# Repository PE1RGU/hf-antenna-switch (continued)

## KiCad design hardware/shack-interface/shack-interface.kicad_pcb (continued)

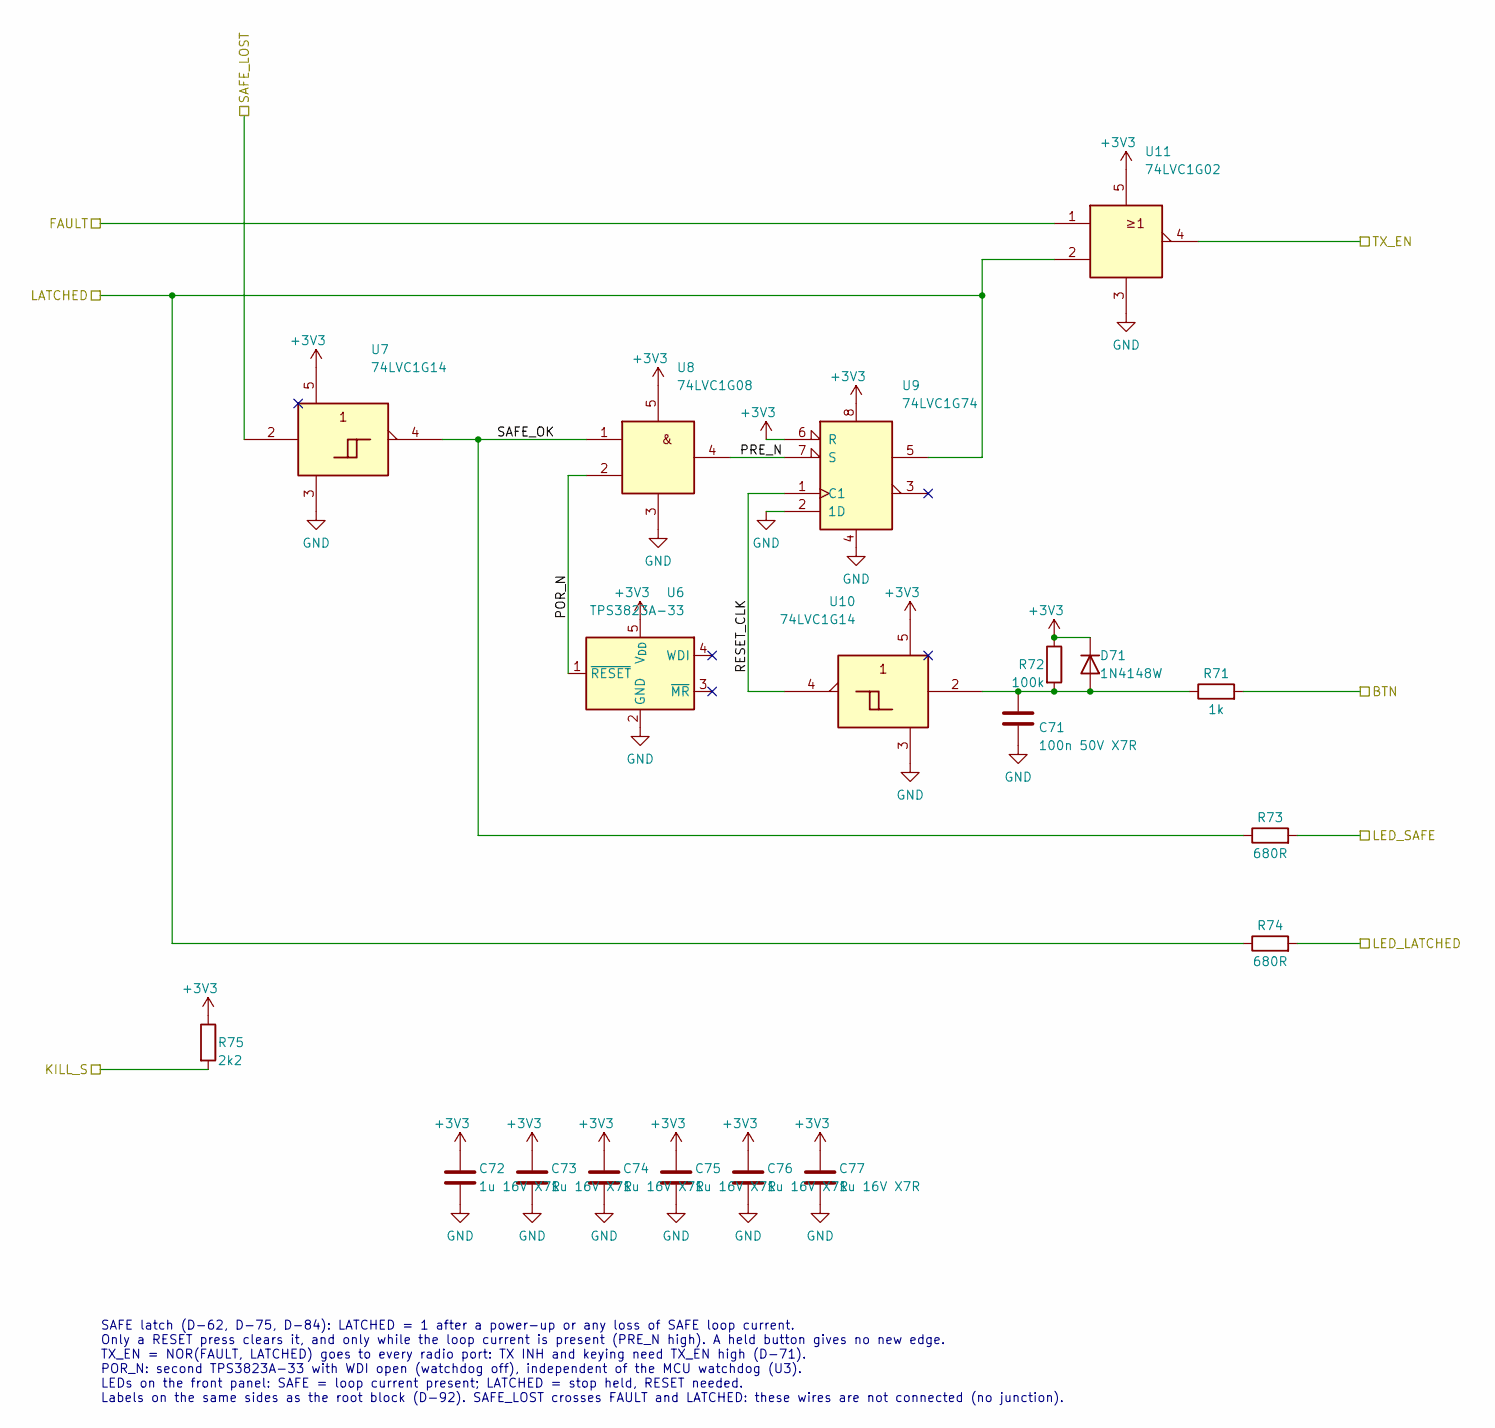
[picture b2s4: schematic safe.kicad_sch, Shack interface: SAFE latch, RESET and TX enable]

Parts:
C71: 100n 50V X7R; C_0603_1608Metric_Pad1.08x0.95mm_HandSolder
C72, C73, C74, C75, C76, C77: 1u 16V X7R; C_0603_1608Metric_Pad1.08x0.95mm_HandSolder
D71: 1N4148W; D_SOD-123; MPN 1N4148W
R71: 1k; R_0603_1608Metric_Pad0.98x0.95mm_HandSolder
R72: 100k; R_0603_1608Metric_Pad0.98x0.95mm_HandSolder
R73, R74: 680R; R_0603_1608Metric_Pad0.98x0.95mm_HandSolder
R75: 2k2; R_0603_1608Metric_Pad0.98x0.95mm_HandSolder
U6: TPS3823A-33; SOT-23-5; MPN TPS3823A-33DBVR
U7, U10: 74LVC1G14; SOT-23-5; MPN 74LVC1G14GV
U8: 74LVC1G08; SOT-23-5; MPN 74LVC1G08GV
U9: 74LVC1G74; VSSOP-8_2.3x2mm_P0.5mm; MPN SN74LVC1G74DCUR
U11: 74LVC1G02; SOT-23-5; MPN 74LVC1G02GV

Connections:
+3V3: C72.1, C73.1, C74.1, C75.1, C76.1, C77.1, D71.1 (K), R72.1, R75.1, U6.5 (V_{DD}), U7.5, U8.5, U9.6 (R), U9.8, U10.5, U11.5; also elsewhere on the board
/MCU and expander/FAULT: U11.1; also elsewhere on the board
/MCU and expander/KILL_S: R75.2; also elsewhere on the board
/MCU and expander/LATCHED: R74.1, U9.5, U11.2; also elsewhere on the board
/MCU and expander/SAFE_LOST: U7.2; also elsewhere on the board
/Radio port R1/TX_EN: U11.4; also elsewhere on the board
/SAFE latch/BTN: R71.2; also elsewhere on the board
/SAFE latch/LED_LATCHED: R74.2; also elsewhere on the board
/SAFE latch/LED_SAFE: R73.2; also elsewhere on the board
/SAFE latch/POR_N: U6.1 (~RESET), U8.2
/SAFE latch/PRE_N: U8.4, U9.7 (S)
/SAFE latch/RESET_CLK: U9.1 (C1), U10.4
/SAFE latch/SAFE_OK: R73.1, U7.4, U8.1
GND: C71.2, C72.2, C73.2, C74.2, C75.2, C76.2, C77.2, U6.2 (GND), U7.3, U8.3, U9.2 (1D), U9.4, U10.3, U11.3; also elsewhere on the board
unnamed: C71.1, D71.2 (A), R71.1, R72.2, U10.2

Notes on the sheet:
SAFE latch (D-62, D-75, D-84): LATCHED = 1 after a power-up or any loss of SAFE loop current. Only a RESET press clears it, and only while the loop current is present (PRE_N high). A held button gives no new edge. TX_EN = NOR(FAULT, LATCHED) goes to every radio port: TX INH and keying need TX_EN hi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

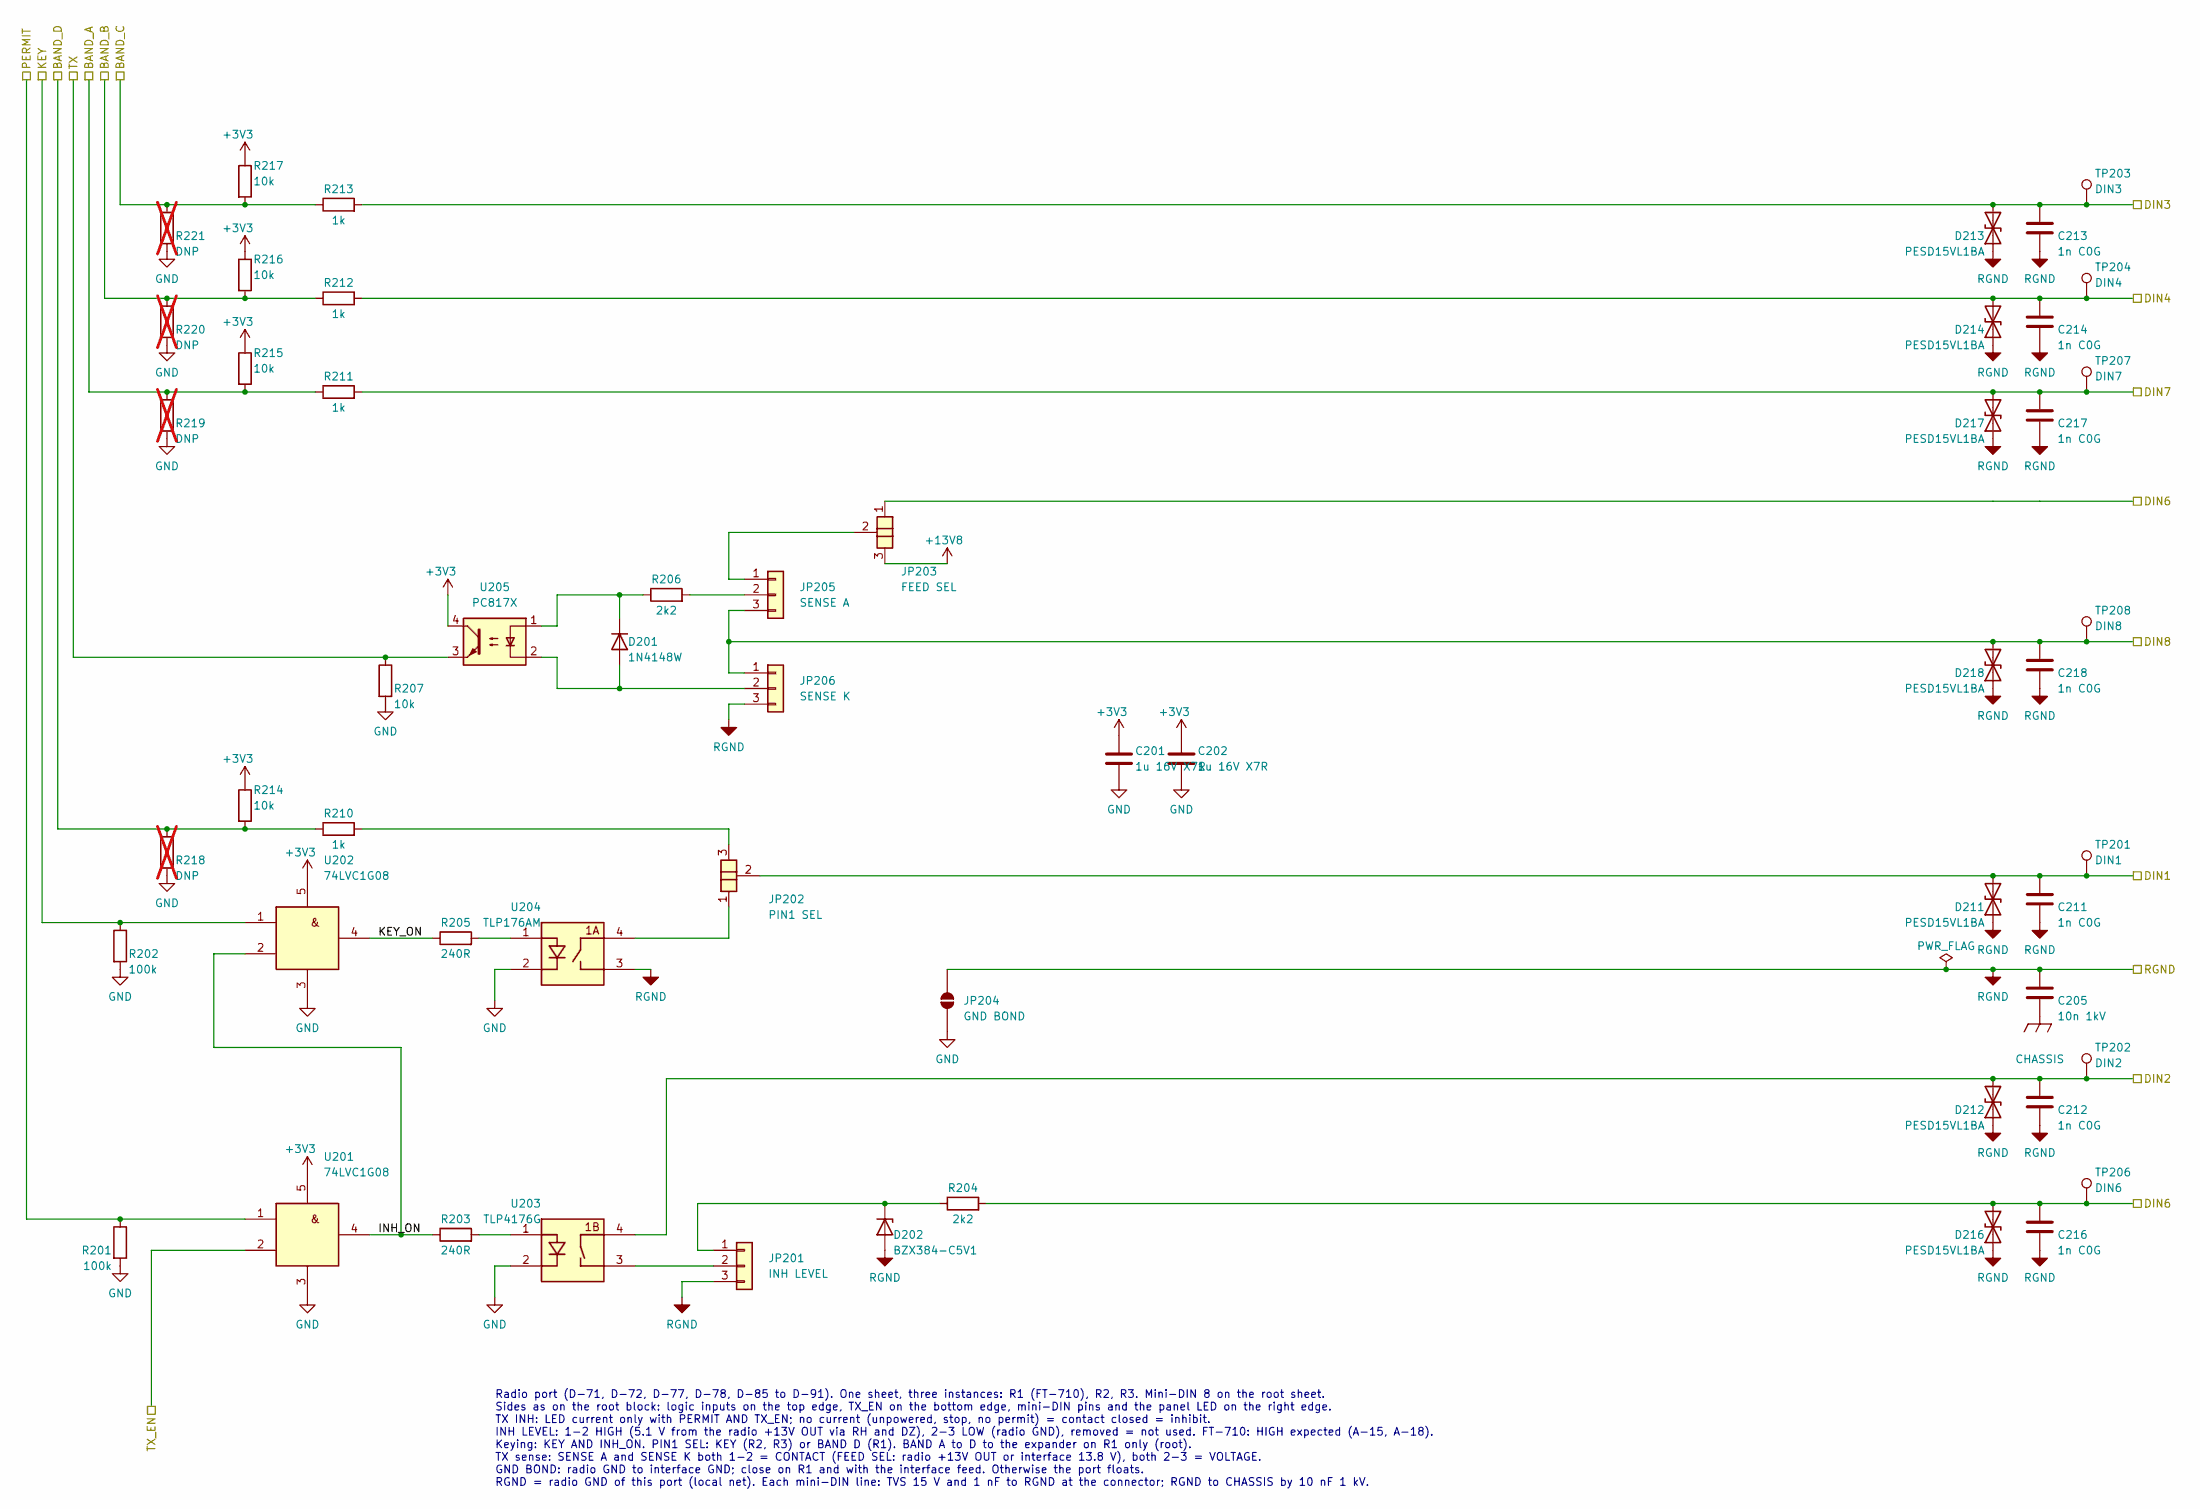
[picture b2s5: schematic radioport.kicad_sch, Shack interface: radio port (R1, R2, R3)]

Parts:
C201, C202: 1u 16V X7R; C_0603_1608Metric_Pad1.08x0.95mm_HandSolder
C205: 10n 1kV; C_1206_3216Metric_Pad1.33x1.80mm_HandSolder
C211, C212, C213, C214, C216, C217, C218: 1n C0G; C_0603_1608Metric_Pad1.08x0.95mm_HandSolder
D201: 1N4148W; D_SOD-123; MPN 1N4148W
D202: BZX384-C5V1; D_SOD-323_HandSoldering; MPN BZX384-C5V1
D211, D212, D213, D214, D216, D217, D218: PESD15VL1BA; D_SOD-323_HandSoldering; MPN PESD15VL1BA
JP201: INH LEVEL; PinHeader_1x03_P2.54mm_Vertical
JP202: PIN1 SEL; SolderJumper-3_P1.3mm_Open_RoundedPad1.0x1.5mm_NumberLabels
JP203: FEED SEL; SolderJumper-3_P1.3mm_Open_RoundedPad1.0x1.5mm_NumberLabels
JP204: GND BOND; SolderJumper-2_P1.3mm_Open_RoundedPad1.0x1.5mm
JP205: SENSE A; PinHeader_1x03_P2.54mm_Vertical
JP206: SENSE K; PinHeader_1x03_P2.54mm_Vertical
R201, R202: 100k; R_0603_1608Metric_Pad0.98x0.95mm_HandSolder
R203, R205: 240R; R_0603_1608Metric_Pad0.98x0.95mm_HandSolder
R204: 2k2; R_0603_1608Metric_Pad0.98x0.95mm_HandSolder
R206: 2k2; R_1206_3216Metric_Pad1.30x1.75mm_HandSolder
R207, R214, R215, R216, R217: 10k; R_0603_1608Metric_Pad0.98x0.95mm_HandSolder
R210, R211, R212, R213: 1k; R_0603_1608Metric_Pad0.98x0.95mm_HandSolder
R218, R219, R220, R221: DNP; R_0603_1608Metric_Pad0.98x0.95mm_HandSolder; not fitted
TP201: DIN1; TestPoint_Pad_D1.5mm
TP202: DIN2; TestPoint_Pad_D1.5mm
TP203: DIN3; TestPoint_Pad_D1.5mm
TP204: DIN4; TestPoint_Pad_D1.5mm
TP206: DIN6; TestPoint_Pad_D1.5mm
TP207: DIN7; TestPoint_Pad_D1.5mm
TP208: DIN8; TestPoint_Pad_D1.5mm
U201, U202: 74LVC1G08; SOT-23-5; MPN 74LVC1G08GV
U203: TLP4176G; SOP-4_P2.54mm_PhotoRelay_LongPad; MPN TLP4176G
U204: TLP176AM; SOP-4_P2.54mm_PhotoRelay_LongPad; MPN TLP176AM(TPL,E)
U205: PC817X; DIP-4_W7.62mm; MPN PC817X2NSZ9F

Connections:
+3V3: C201.1, C202.1, R214.1, R215.1, R216.1, R217.1, U201.5, U202.5, U205.4; also elsewhere on the board
+13V8: JP203.3; also elsewhere on the board
/Link to the box/R1_TX: R207.1, U205.3; also elsewhere on the board
/MCU and expander/BAND_A: R211.1, R215.2, R219.1; also elsewhere on the board
/MCU and expander/BAND_B: R212.1, R216.2, R220.1; also elsewhere on the board
/MCU and expander/BAND_C: R213.1, R217.2, R221.1; also elsewhere on the board
/MCU and expander/BAND_D: R210.1, R214.2, R218.1; also elsewhere on the board
/MCU and expander/KEY_R1: R202.1, U202.1; also elsewhere on the board
/MCU and expander/PERMIT_R1: R201.1, U201.1; also elsewhere on the board
/Radio port R1/DIN1: C211.1, D211.2 (A2), JP202.2, TP201.1; also elsewhere on the board
/Radio port R1/DIN2: C212.1, D212.2 (A2), TP202.1, U203.4; also elsewhere on the board
/Radio port R1/DIN3: C213.1, D213.2 (A2), R213.2, TP203.1; also elsewhere on the board
/Radio port R1/DIN4: C214.1, D214.2 (A2), R212.2, TP204.1; also elsewhere on the board
/Radio port R1/DIN6: C216.1, D216.2 (A2), JP203.1, R204.2, TP206.1; also elsewhere on the board
/Radio port R1/DIN7: C217.1, D217.2 (A2), R211.2, TP207.1; also elsewhere on the board
/Radio port R1/DIN8: C218.1, D218.2 (A2), JP205.3, JP206.1, TP208.1; also elsewhere on the board
/Radio port R1/INH_ON: R203.1, U201.4, U202.2
/Radio port R1/KEY_ON: R205.1, U202.4
/Radio port R1/RGND: C205.1, C211.2, C212.2, C213.2, C214.2, C216.2, C217.2, C218.2, D202.2 (A), D211.1 (A1), D212.1 (A1), D213.1 (A1), D214.1 (A1), D216.1 (A1), D217.1 (A1), D218.1 (A1), JP201.3, JP204.2 (B), JP206.3, U204.3; also elsewhere on the board
/Radio port R1/TX_EN: U201.2; also elsewhere on the board
CHASSIS: C205.2; also elsewhere on the board
GND: C201.2, C202.2, JP204.1 (A), R201.2, R202.2, R207.2, R218.2, R219.2, R220.2, R221.2, U201.3, U202.3, U203.2, U204.2; also elsewhere on the board
unnamed: D201.2 (A), JP206.2, U205.2
unnamed: D201.1 (K), R206.1, U205.1
unnamed: D202.1 (K), JP201.1, R204.1
unnamed: JP201.2, U203.3
unnamed: JP202.1, U204.4
unnamed: JP202.3, R210.2
unnamed: JP203.2, JP205.1
unnamed: JP205.2, R206.2
unnamed: R203.2, U203.1
unnamed: R205.2, U204.1

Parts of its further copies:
C301, C302, C401, C402: 1u 16V X7R; C_0603_1608Metric_Pad1.08x0.95mm_HandSolder
C305, C405: 10n 1kV; C_1206_3216Metric_Pad1.33x1.80mm_HandSolder
C311, C312, C313, C314, C316, C317, C318, C411, C412, C413, C414, C416, C417, C418: 1n C0G; C_0603_1608Metric_Pad1.08x0.95mm_HandSolder
D301, D401: 1N4148W; D_SOD-123; MPN 1N4148W
D302, D402: BZX384-C5V1; D_SOD-323_HandSoldering; MPN BZX384-C5V1
D311, D312, D313, D314, D316, D317, D318, D411, D412, D413, D414, D416, D417, D418: PESD15VL1BA; D_SOD-323_HandSoldering; MPN PESD15VL1BA
JP301, JP401: INH LEVEL; PinHeader_1x03_P2.54mm_Vertical
JP302, JP402: PIN1 SEL; SolderJumper-3_P1.3mm_Open_RoundedPad1.0x1.5mm_NumberLabels
JP303, JP403: FEED SEL; SolderJumper-3_P1.3mm_Open_RoundedPad1.0x1.5mm_NumberLabels
JP304, JP404: GND BOND; SolderJumper-2_P1.3mm_Open_RoundedPad1.0x1.5mm
JP305, JP405: SENSE A; PinHeader_1x03_P2.54mm_Vertical
JP306, JP406: SENSE K; PinHeader_1x03_P2.54mm_Vertical
R301, R302, R401, R402: 100k; R_0603_1608Metric_Pad0.98x0.95mm_HandSolder
R303, R305, R403, R405: 240R; R_0603_1608Metric_Pad0.98x0.95mm_HandSolder
R304, R404: 2k2; R_0603_1608Metric_Pad0.98x0.95mm_HandSolder
R306, R406: 2k2; R_1206_3216Metric_Pad1.30x1.75mm_HandSolder
R307, R314, R315, R316, R317, R407, R414, R415, R416, R417: 10k; R_0603_1608Metric_Pad0.98x0.95mm_HandSolder
R310, R311, R312, R313, R410, R411, R412, R413: 1k; R_0603_1608Metric_Pad0.98x0.95mm_HandSolder
R318, R319, R320, R321, R418, R419, R420, R421: DNP; R_0603_1608Metric_Pad0.98x0.95mm_HandSolder; not fitted
TP301, TP401: DIN1; TestPoint_Pad_D1.5mm
TP302, TP402: DIN2; TestPoint_Pad_D1.5mm
TP303, TP403: DIN3; TestPoint_Pad_D1.5mm
TP304, TP404: DIN4; TestPoint_Pad_D1.5mm
TP306, TP406: DIN6; TestPoint_Pad_D1.5mm
TP307, TP407: DIN7; TestPoint_Pad_D1.5mm
TP308, TP408: DIN8; TestPoint_Pad_D1.5mm
U301, U302, U401, U402: 74LVC1G08; SOT-23-5; MPN 74LVC1G08GV
U303, U403: TLP4176G; SOP-4_P2.54mm_PhotoRelay_LongPad; MPN TLP4176G
U304, U404: TLP176AM; SOP-4_P2.54mm_PhotoRelay_LongPad; MPN TLP176AM(TPL,E)
U305, U405: PC817X; DIP-4_W7.62mm; MPN PC817X2NSZ9F

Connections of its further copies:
+3V3: C301.1, C302.1, C401.1, C402.1, R314.1, R315.1, R316.1, R317.1, R414.1, R415.1, R416.1, R417.1, U301.5, U302.5, U305.4, U401.5, U402.5, U405.4; also elsewhere on the board
+13V8: JP303.3, JP403.3; also elsewhere on the board
/MCU and expander/KEY_R2: R302.1, U302.1; also elsewhere on the board
/MCU and expander/KEY_R3: R402.1, U402.1; also elsewhere on the board
/MCU and expander/PERMIT_R2: R301.1, U301.1; also elsewhere on the board
/MCU and expander/PERMIT_R3: R401.1, U401.1; also elsewhere on the board
/MCU and expander/R2_TX: R307.1, U305.3; also elsewhere on the board
/MCU and expander/R3_TX: R407.1, U405.3; also elsewhere on the board
/Radio port R1/TX_EN: U301.2, U401.2; also elsewhere on the board
/Radio port R2/BAND_A: R311.1, R315.2, R319.1
/Radio port R2/BAND_B: R312.1, R316.2, R320.1
/Radio port R2/BAND_C: R313.1, R317.2, R321.1
/Radio port R2/BAND_D: R310.1, R314.2, R318.1
/Radio port R2/DIN1: C311.1, D311.2 (A2), JP302.2, TP301.1; also elsewhere on the board
/Radio port R2/DIN2: C312.1, D312.2 (A2), TP302.1, U303.4; also elsewhere on the board
/Radio port R2/DIN3: C313.1, D313.2 (A2), R313.2, TP303.1; also elsewhere on the board
/Radio port R2/DIN4: C314.1, D314.2 (A2), R312.2, TP304.1; also elsewhere on the board
/Radio port R2/DIN6: C316.1, D316.2 (A2), JP303.1, R304.2, TP306.1; also elsewhere on the board
/Radio port R2/DIN7: C317.1, D317.2 (A2), R311.2, TP307.1; also elsewhere on the board
/Radio port R2/DIN8: C318.1, D318.2 (A2), JP305.3, JP306.1, TP308.1; also elsewhere on the board
/Radio port R2/INH_ON: R303.1, U301.4, U302.2
/Radio port R2/KEY_ON: R305.1, U302.4
/Radio port R2/RGND: C305.1, C311.2, C312.2, C313.2, C314.2, C316.2, C317.2, C318.2, D302.2 (A), D311.1 (A1), D312.1 (A1), D313.1 (A1), D314.1 (A1), D316.1 (A1), D317.1 (A1), D318.1 (A1), JP301.3, JP304.2 (B), JP306.3, U304.3; also elsewhere on the board
/Radio port R3/BAND_A: R411.1, R415.2, R419.1
/Radio port R3/BAND_B: R412.1, R416.2, R420.1
/Radio port R3/BAND_C: R413.1, R417.2, R421.1
/Radio port R3/BAND_D: R410.1, R414.2, R418.1
/Radio port R3/DIN1: C411.1, D411.2 (A2), JP402.2, TP401.1; also elsewhere on the board
/Radio port R3/DIN2: C412.1, D412.2 (A2), TP402.1, U403.4; also elsewhere on the board
/Radio port R3/DIN3: C413.1, D413.2 (A2), R413.2, TP403.1; also elsewhere on the board
/Radio port R3/DIN4: C414.1, D414.2 (A2), R412.2, TP404.1; also elsewhere on the board
/Radio port R3/DIN6: C416.1, D416.2 (A2), JP403.1, R404.2, TP406.1; also elsewhere on the board
/Radio port R3/DIN7: C417.1, D417.2 (A2), R411.2, TP407.1; also elsewhere on the board
/Radio port R3/DIN8: C418.1, D418.2 (A2), JP405.3, JP406.1, TP408.1; also elsewhere on the board
/Radio port R3/INH_ON: R403.1, U401.4, U402.2
/Radio port R3/KEY_ON: R405.1, U402.4
/Radio port R3/RGND: C405.1, C411.2, C412.2, C413.2, C414.2, C416.2, C417.2, C418.2, D402.2 (A), D411.1 (A1), D412.1 (A1), D413.1 (A1), D414.1 (A1), D416.1 (A1), D417.1 (A1), D418.1 (A1), JP401.3, JP404.2 (B), JP406.3, U404.3; also elsewhere on the board
CHASSIS: C305.2, C405.2; also elsewhere on the board
GND: C301.2, C302.2, C401.2, C402.2, JP304.1 (A), JP404.1 (A), R301.2, R302.2, R307.2, R318.2, R319.2, R320.2, R321.2, R401.2, R402.2, R407.2, R418.2, R419.2, R420.2, R421.2, U301.3, U302.3, U303.2, U304.2, U401.3, U402.3, U403.2, U404.2; also elsewhere on the board
unnamed: D301.2 (A), JP306.2, U305.2
unnamed: D301.1 (K), R306.1, U305.1
unnamed: D302.1 (K), JP301.1, R304.1
unnamed: D401.2 (A), JP406.2, U405.2
unnamed: D401.1 (K), R406.1, U405.1
unnamed: D402.1 (K), JP401.1, R404.1
unnamed: JP301.2, U303.3
unnamed: JP302.1, U304.4
unnamed: JP302.3, R310.2
unnamed: JP303.2, JP305.1
unnamed: JP305.2, R306.2
unnamed: JP401.2, U403.3
unnamed: JP402.1, U404.4
unnamed: JP402.3, R410.2
unnamed: JP403.2, JP405.1
unnamed: JP405.2, R406.2
unnamed: R303.2, U303.1
unnamed: R305.2, U304.1
unnamed: R403.2, U403.1
unnamed: R405.2, U404.1

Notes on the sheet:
Radio port (D-71, D-72, D-77, D-78, D-85 to D-91). One sheet, three instances: R1 (FT-710), R2, R3. Mini-DIN 8 on the root sheet. Sides as on the root block: logic inputs on the top edge, TX_EN on the bottom edge, mini-DIN pins and the panel LED on the right edge. TX INH: LED current only with PERM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

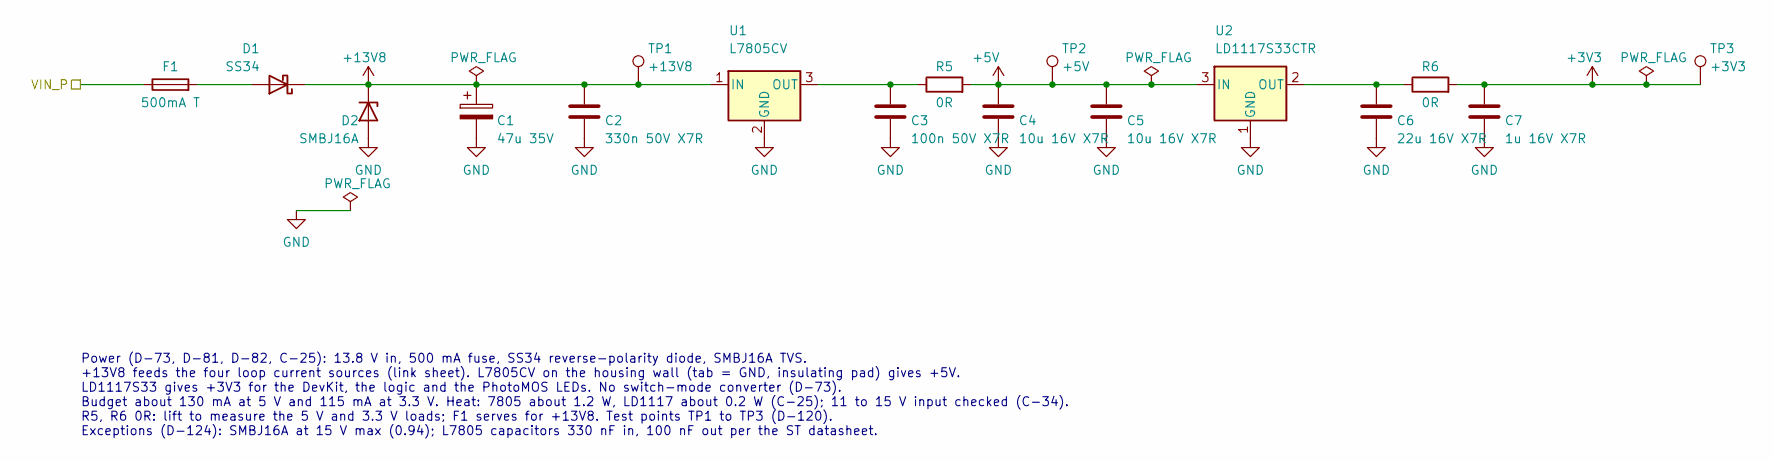
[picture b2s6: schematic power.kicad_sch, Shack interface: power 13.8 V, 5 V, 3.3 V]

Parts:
C1: 47u 35V; CP_Radial_D6.3mm_P2.50mm
C2: 330n 50V X7R; C_0805_2012Metric_Pad1.18x1.45mm_HandSolder
C3: 100n 50V X7R; C_0603_1608Metric_Pad1.08x0.95mm_HandSolder
C4, C5: 10u 16V X7R; C_1206_3216Metric_Pad1.33x1.80mm_HandSolder
C6: 22u 16V X7R; C_1210_3225Metric_Pad1.33x2.70mm_HandSolder
C7: 1u 16V X7R; C_0603_1608Metric_Pad1.08x0.95mm_HandSolder
D1: SS34; D_SMC; MPN SS34-M3/57T
D2: SMBJ16A; D_SMB; MPN SMBJ16A
F1: 500mA T; Fuse_1206_3216Metric; MPN SF-1206S050
R5, R6: 0R; R_1206_3216Metric_Pad1.30x1.75mm_HandSolder
TP1: +13V8; TestPoint_Pad_D1.5mm
TP2: +5V; TestPoint_Pad_D1.5mm
TP3: +3V3; TestPoint_Pad_D1.5mm
U1: L7805CV; TO-220-3_Vertical; MPN L7805CV
U2: LD1117S33CTR; SOT-223-3_TabPin2; MPN LD1117S33CTR

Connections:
+3V3: C7.1, R6.2, TP3.1; also elsewhere on the board
+5V: C4.1, C5.1, R5.2, TP2.1, U2.3 (IN)
+13V8: C1.1, C2.1, D1.1 (K), D2.1 (K), TP1.1, U1.1 (IN); also elsewhere on the board
/Power/VIN_P: F1.1; also elsewhere on the board
GND: C1.2, C2.2, C3.2, C4.2, C5.2, C6.2, C7.2, D2.2 (A), U1.2 (GND), U2.1 (GND); also elsewhere on the board
unnamed: D1.2 (A), F1.2
unnamed: C3.1, R5.1, U1.3 (OUT)
unnamed: C6.1, R6.1, U2.2 (OUT)

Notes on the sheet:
Power (D-73, D-81, D-82, C-25): 13.8 V in, 500 mA fuse, SS34 reverse-polarity diode, SMBJ16A TVS. +13V8 feeds the four loop current sources (link sheet). L7805CV on the housing wall (tab = GND, insulating pad) gives +5V. LD1117S33 gives +3V3 for the DevKit, the logic and the PhotoMOS LEDs. No switc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

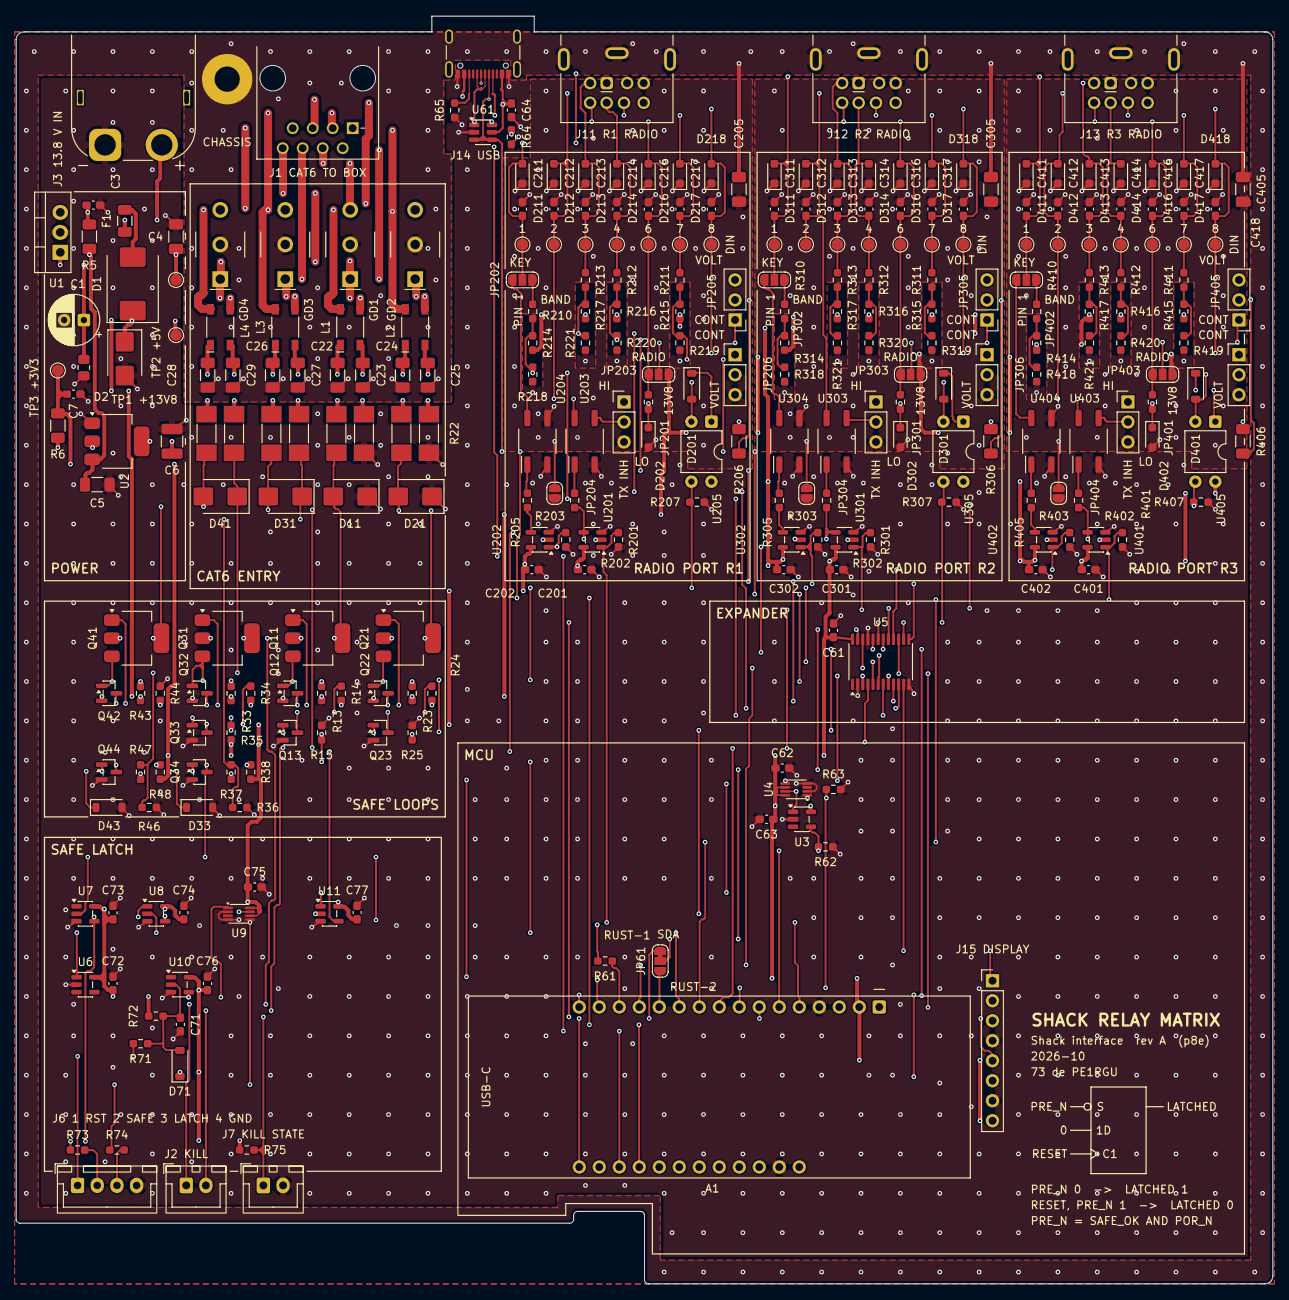
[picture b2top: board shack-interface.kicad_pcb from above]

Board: 4 copper layers, 159.6 x 161.0 mm, 290 parts (0 on the bottom side), 160 nets.

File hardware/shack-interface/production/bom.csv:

Designator,Footprint,Quantity,Value,LCSC Part #
A1,ESP32-C3-DevKit-RUST_Socket,1,ESP32-C3-DevKit-RUST-1,
C1,CP_Radial_D6.3mm_P2.50mm,1,47u 35V,
C2,0805,1,330n 50V X7R,
"C201, C202, C301, C302, C401, C402, C61, C62, C63, C7, C72, C73, C74, C75, C76, C77",0603,16,1u 16V X7R,
"C205, C305, C405",1206,3,10n 1kV,
"C211, C212, C213, C214, C216, C217, C218, C311, C312, C313, C314, C316, C317, C318, C411, C412, C413, C414, C416, C417, C418",0603,21,1n C0G,
"C3, C64, C71",0603,3,100n 50V X7R,
"C4, C5",1206,2,10u 16V X7R,
C6,1210,1,22u 16V X7R,
D1,D_SMC,1,SS34,
"D11, D21, D31, D41",D_SMB,4,SMBJ15CA,
D2,D_SMB,1,SMBJ16A,
"D201, D301, D33, D401, D43, D71",D_SOD-123,6,1N4148W,
"D202, D302, D402",D_SOD-323_HandSoldering,3,BZX384-C5V1,
"D211, D212, D213, D214, D216, D217, D218, D311, D312, D313, D314, D316, D317, D318, D411, D412, D413, D414, D416, D417, D418",D_SOD-323_HandSoldering,21,PESD15VL1BA,
F1,1206,1,500mA T,
"GD1, GD2, GD3, GD4",GDT_3Pin_P4.40mm_Bourns-2036-B2_Littelfuse-SL1003A-R,4,2036-09-B2LF,
J1,RJ45_8P8C_Unshielded_TabDown,1,RJ45 LINK,
J11,MiniDIN-8_SameSky_MD-80SM_Horizontal,1,R1 mini-DIN,
J12,MiniDIN-8_SameSky_MD-80SM_Horizontal,1,R2 mini-DIN,
J13,MiniDIN-8_SameSky_MD-80SM_Horizontal,1,R3 mini-DIN,
J14,USB_C_Receptacle_GCT_USB4105-xx-A_16P_TopMnt_Horizontal,1,USB4105-GF-A,
J15,PinHeader_1x08_P2.54mm_Vertical,1,DISPLAY,
J2,JST_XH_B2B-XH-A_1x02_P2.50mm_Vertical,1,KILL switch,
J3,AMASS_XT60PW-M_1x02_P7.20mm_Horizontal,1,13.8 V IN,
J6,JST_XH_B4B-XH-A_1x04_P2.50mm_Vertical,1,Front panel,
J7,JST_XH_B2B-XH-A_1x02_P2.50mm_Vertical,1,KILL state,
"JP201, JP301, JP401",PinHeader_1x03_P2.54mm_Vertical,3,INH LEVEL,
"JP202, JP302, JP402",SolderJumper-3_P1.3mm_Open_RoundedPad1.0x1.5mm_NumberLabels,3,PIN1 SEL,
"JP203, JP303, JP403",SolderJumper-3_P1.3mm_Open_RoundedPad1.0x1.5mm_NumberLabels,3,FEED SEL,
"JP204, JP304, JP404",SolderJumper-2_P1.3mm_Open_RoundedPad1.0x1.5mm,3,GND BOND,
"JP205, JP305, JP405",PinHeader_1x03_P2.54mm_Vertical,3,SENSE A,
"JP206, JP306, JP406",PinHeader_1x03_P2.54mm_Vertical,3,SENSE K,
JP61,SolderJumper-3_P1.3mm_Bridged12_RoundedPad1.0x1.5mm_NumberLabels,1,SDA SEL,
"L1, L2, L3, L4",L_CMC_TDK_ACT45B,4,51u CMC,
"Q11, Q21, Q31, Q41",SOT-223-3_TabPin2,4,BCP53-16,
"Q12, Q22, Q32, Q42",SOT-23,4,BC857B,
"Q13, Q23, Q33",SOT-23,3,BSS138BK,
"Q34, Q44",SOT-23,2,BC847B,
"R11, R12, R21, R22, R31, R32, R41, R42",R_MELF_MMB-0207,8,47R,
"R13, R23, R33, R43",0603,4,56R,
"R14, R24, R34, R44",0603,4,22k,
"R15, R201, R202, R25, R301, R302, R35, R401, R402, R63, R72",0603,11,100k,
"R203, R205, R303, R305, R403, R405",0603,6,240R,
"R204, R304, R404, R75",0603,4,2k2,
"R206, R306, R406",1206,3,2k2,
"R207, R214, R215, R216, R217, R307, R314, R315, R316, R317, R38, R407, R414, R415, R416, R417, R48",0603,17,10k,
"R210, R211, R212, R213, R310, R311, R312, R313, R37, R410, R411, R412, R413, R47, R61, R62, R71",0603,17,1k,
"R36, R46",0603,2,100R,
"R5, R6",1206,2,0R,
"R64, R65",0603,2,5k1,
"R73, R74",0603,2,680R,
U1,TO-220-3_Vertical,1,L7805CV,
"U10, U7",SOT-23-5,2,74LVC1G14,
U11,SOT-23-5,1,74LVC1G02,
U2,SOT-223-3_TabPin2,1,LD1117S33CTR,
"U201, U202, U301, U302, U401, U402, U8",SOT-23-5,7,74LVC1G08,
"U203, U303, U403",SOP-4_P2.54mm_PhotoRelay_LongPad,3,TLP4176G,
"U204, U304, U404",SOP-4_P2.54mm_PhotoRelay_LongPad,3,TLP176AM,
"U205, U305, U405",DIP-4_W7.62mm,3,PC817X,
"U3, U6",SOT-23-5,2,TPS3823A-33,
"U4, U9",VSSOP-8_2.3x2mm_P0.5mm,2,74LVC1G74,
U5,TSSOP-24_4.4x7.8mm_P0.65mm,1,PCA9539,
U61,SOT-23-6,1,USBLC6-2SC6,

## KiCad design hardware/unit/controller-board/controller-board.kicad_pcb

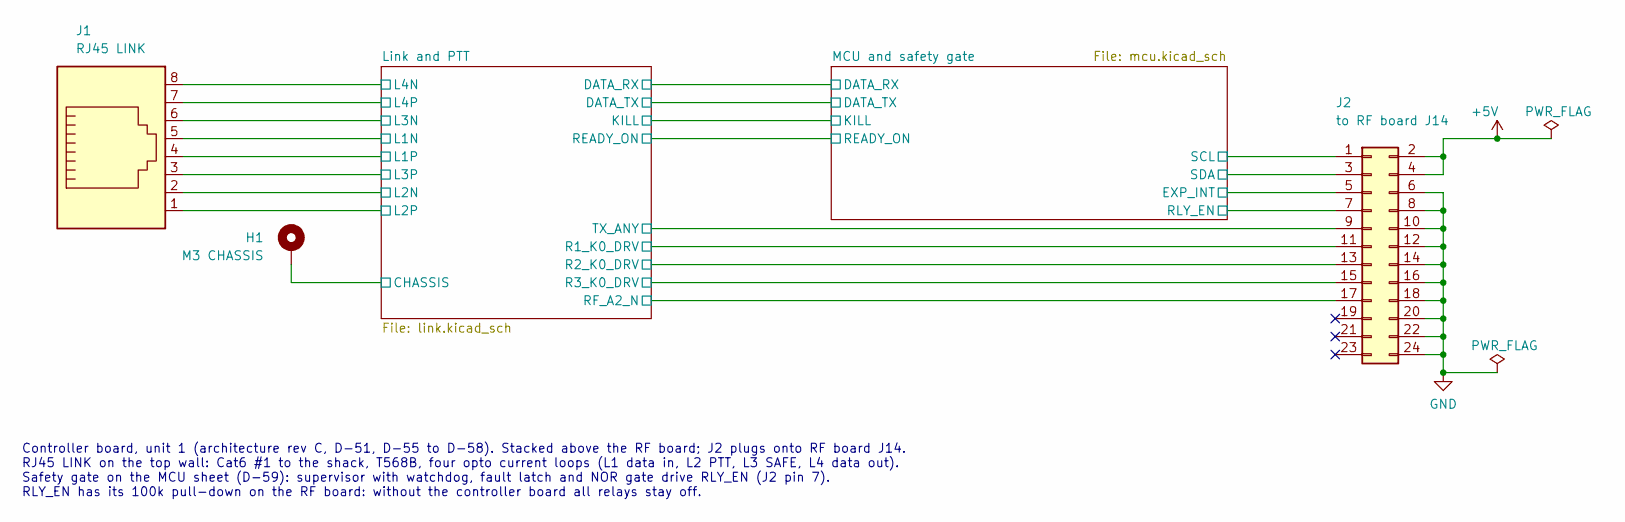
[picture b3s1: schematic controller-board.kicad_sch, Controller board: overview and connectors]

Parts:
H1: M3 CHASSIS; MountingHole_3.2mm_M3_Pad
J1: RJ45 LINK; RJ45_8P8C_Unshielded_TabDown; MPN 615008137121
J2: to RF board J14; PinSocket_2x12_P2.54mm_Vertical; MPN ESQ-112-33-G-D

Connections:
+5V: J2.2, J2.4; also elsewhere on the board
/Link and PTT/CHASSIS: H1.1; also elsewhere on the board
/Link and PTT/L1N: J1.5; also elsewhere on the board
/Link and PTT/L1P: J1.4; also elsewhere on the board
/Link and PTT/L2N: J1.2; also elsewhere on the board
/Link and PTT/L2P: J1.1; also elsewhere on the board
/Link and PTT/L3N: J1.6; also elsewhere on the board
/Link and PTT/L3P: J1.3; also elsewhere on the board
/Link and PTT/L4N: J1.8; also elsewhere on the board
/Link and PTT/L4P: J1.7; also elsewhere on the board
/Link and PTT/R1_K0_DRV: J2.11; also elsewhere on the board
/Link and PTT/R2_K0_DRV: J2.13; also elsewhere on the board
/Link and PTT/R3_K0_DRV: J2.15; also elsewhere on the board
/Link and PTT/RF_A2_N: J2.17; also elsewhere on the board
/Link and PTT/TX_ANY: J2.9; also elsewhere on the board
/MCU and safety gate/EXP_INT: J2.5; also elsewhere on the board
/MCU and safety gate/RLY_EN: J2.7; also elsewhere on the board
/MCU and safety gate/SCL: J2.1; also elsewhere on the board
/MCU and safety gate/SDA: J2.3; also elsewhere on the board
GND: J2.6, J2.8, J2.10, J2.12, J2.14, J2.16, J2.18, J2.20, J2.22, J2.24; also elsewhere on the board

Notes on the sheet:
Controller board, unit 1 (architecture rev C, D-51, D-55 to D-58). Stacked above the RF board; J2 plugs onto RF board J14. RJ45 LINK on the top wall: Cat6 #1 to the shack, T568B, four opto current loops (L1 data in, L2 PTT, L3 SAFE, L4 data out). Safety gate on the MCU sheet (D-59): supervisor with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
